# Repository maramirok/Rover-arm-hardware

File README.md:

# Rover Arm Hardware

Custom motor control PCB for the Space Concordia Mars rover robotic arm, designed in KiCad.

## Overview

The board drives five independent DC motors on the rover arm, receives commands over CAN from the main rover controller, and provides regulated power rails for the MCU and peripherals.

## Specifications

- **MCU:** STM32G030C8T6
- **CAN controller/transceiver:** MCP25625 (SPI interface)
- **Motor outputs:** 5 independent channels with PWM speed control and direction signals
- **Power input:** 16V DC
- **Regulation:** Buck converter  + LDO (MCU/logic supply)

## Contents

- `Schematics/` — KiCad schematic files
- `PCB/` — KiCad PCB layout files
- `Gerbers/` — Fabrication output files
- `BOM/` — Bill of materials

## Tools

Designed in KiCad. Open the project file in KiCad to view schematics and layout.

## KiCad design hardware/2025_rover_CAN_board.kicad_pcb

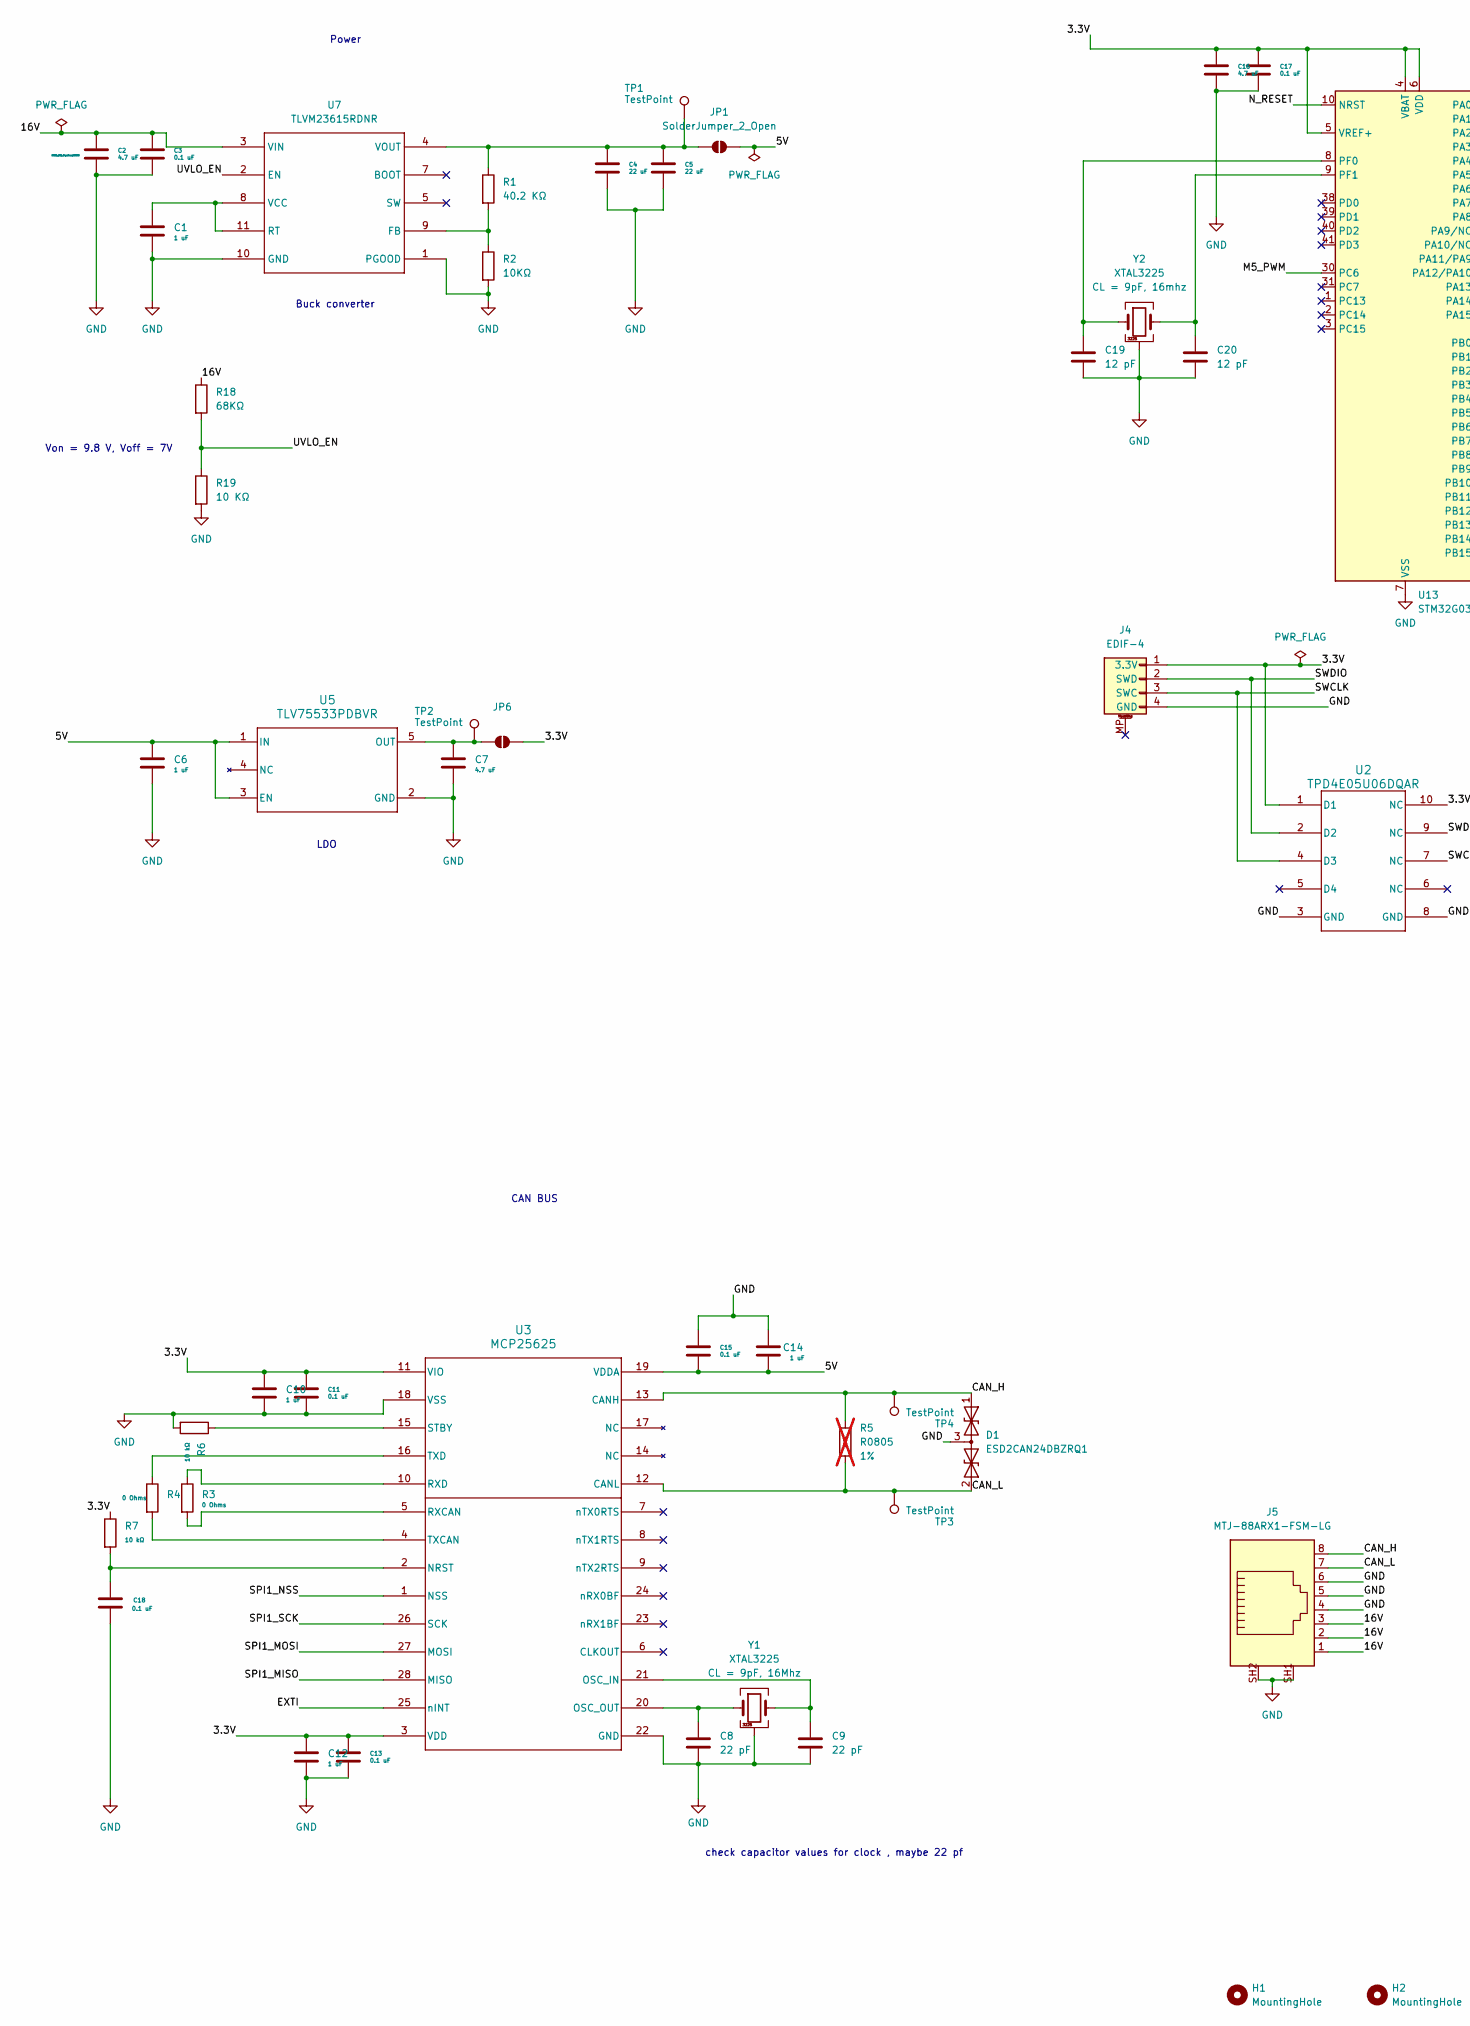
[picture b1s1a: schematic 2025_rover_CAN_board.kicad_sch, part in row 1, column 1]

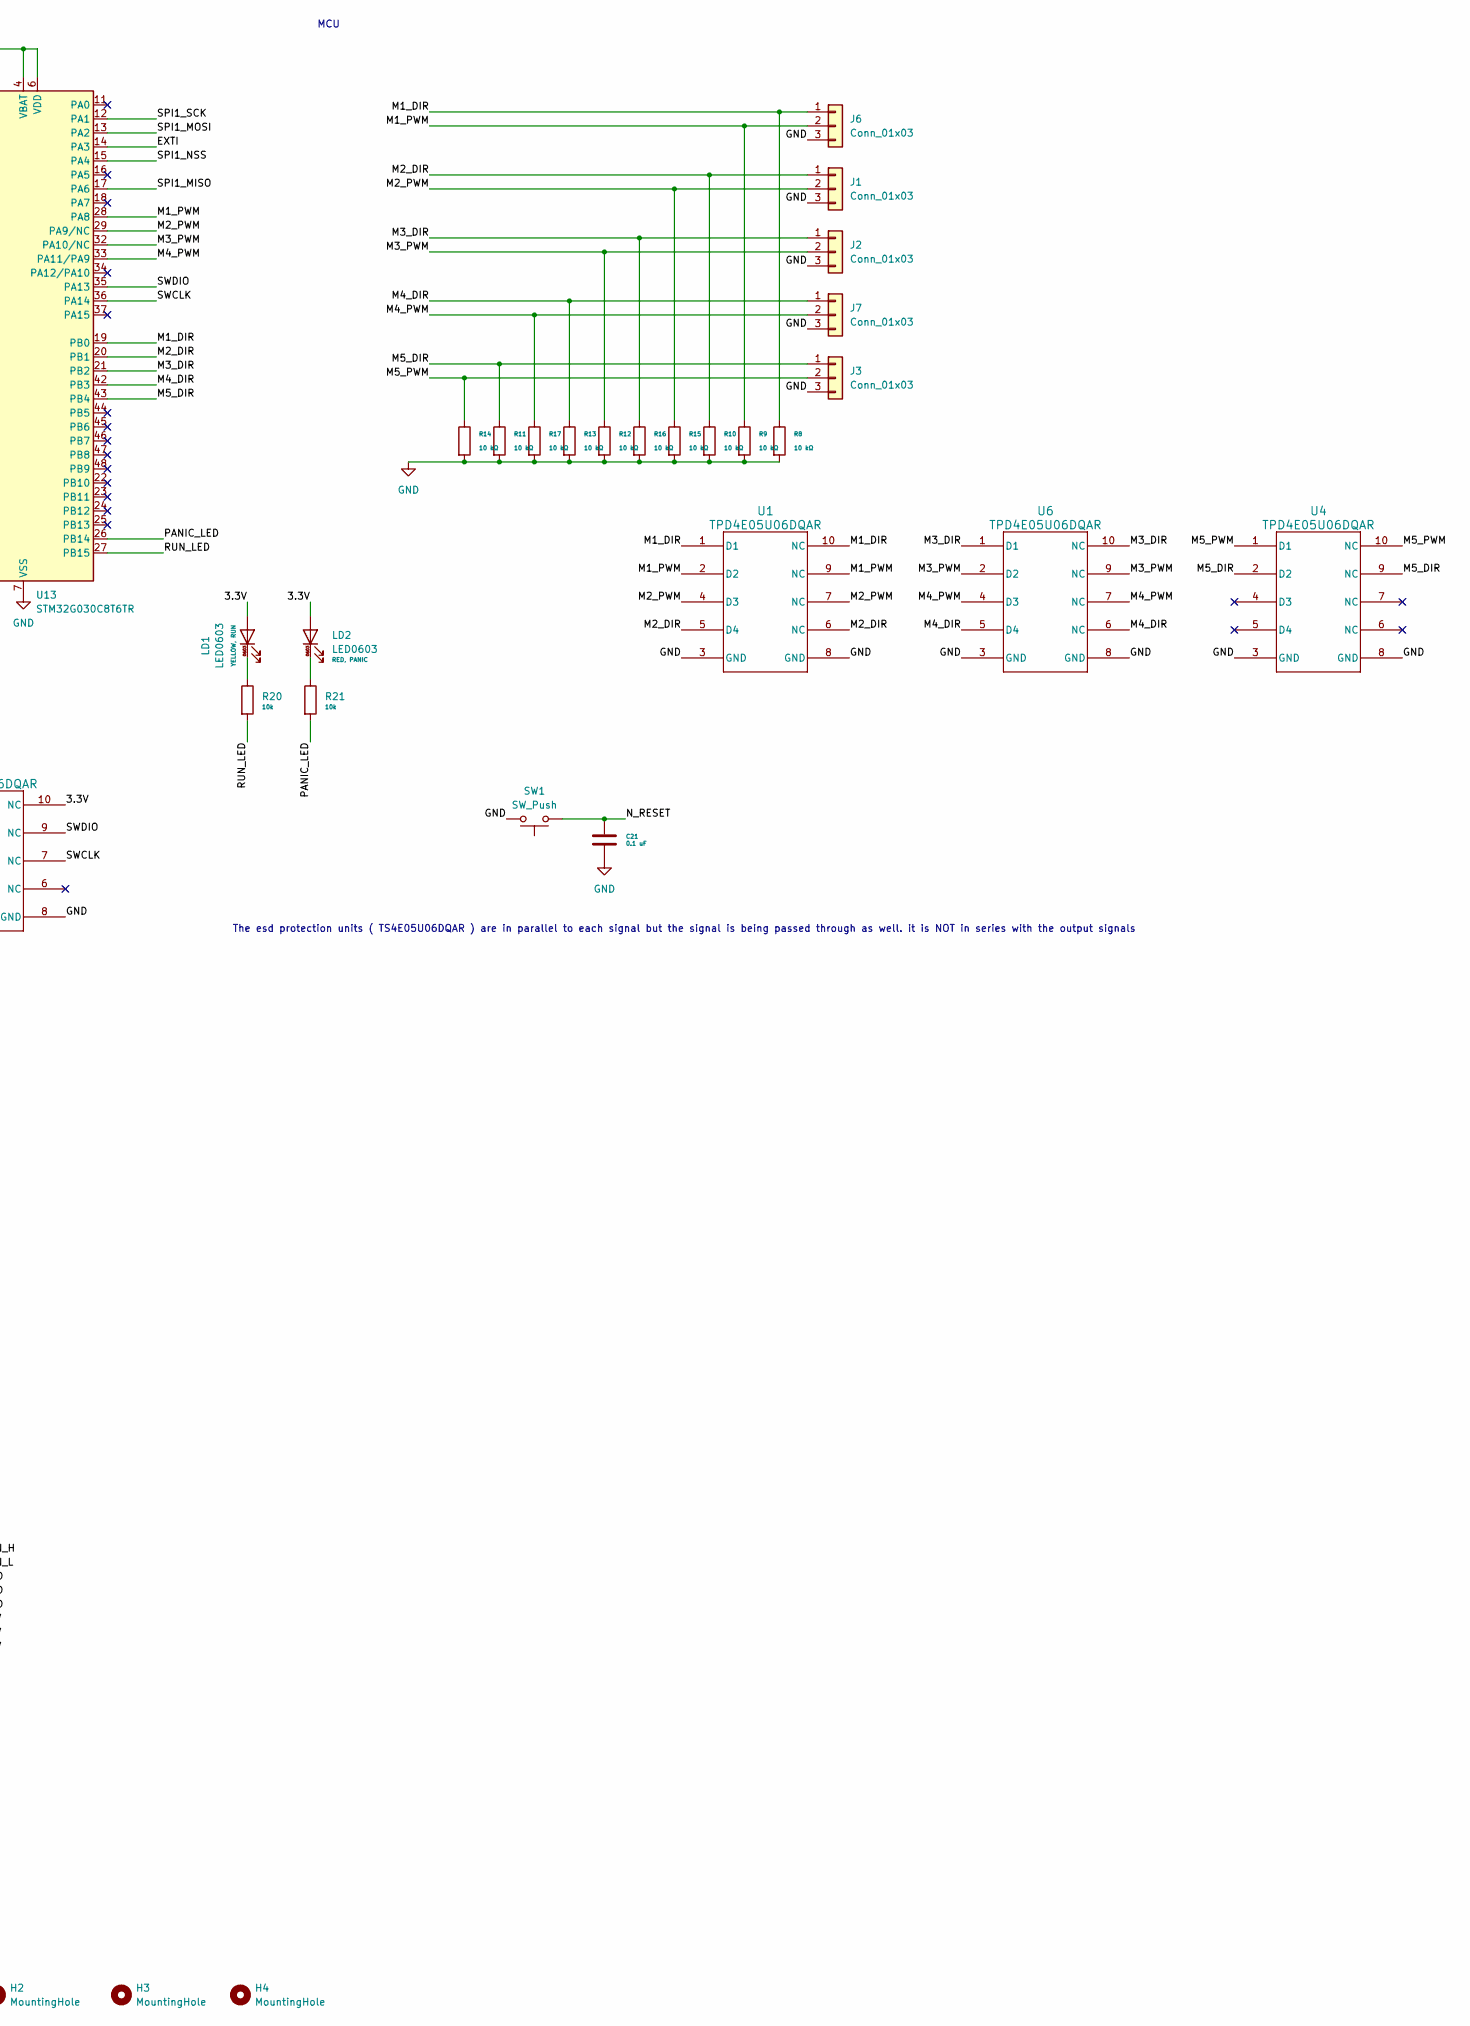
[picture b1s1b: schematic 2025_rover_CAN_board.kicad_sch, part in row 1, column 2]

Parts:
C1, C10, C12, C14: 1 uF; C0402
C2, C7, C16: 4.7 uF; C0805
C3, C11, C13, C15, C17, C18: 0.1 uF; C0402
C4, C5: 22 uF; C0805
C6: 1 uF; C0805
C8, C9: 22 pF; C0402
C19, C20: 12 pF; C0402
C21: 0.1 uF; C0603
D1: ESD2CAN24DBZRQ1; SOT-23_DBZ_TEX
H1, H2, H3, H4: MountingHole; MountingHole_3.2mm_M3
J1, J2, J3, J6, J7: Conn_01x03; JST_XH_S3B-XH-A-1_1x03_P2.50mm_Horizontal
J4: EDIF-4; JST-GH-BM04B-GHS-TBT
J5: MTJ-88ARX1-FSM-LG; ADAMTECH_MTJ-88ARX1-FSM-LG
JP1, JP6: SolderJumper_2_Open; SolderJumper-2_P1.3mm_Open_TrianglePad1.0x1.5mm
LD1, LD2: LED0603
R1: 40.2 KΩ; R0402
R2: 10KΩ; R0402
R3, R4: 0 Ohms; R0402
R5: R0805; not fitted
R6: 10 kΩ; R0805
R7, R8, R9, R10, R11, R12, R13, R14, R15, R16, R17: 10 kΩ; R0402
R18: 68KΩ; R0402
R19: 10 KΩ; R0402
R20, R21: 10k; R0402
SW1: SW_Push; SW_C913791
TP1, TP2, TP3, TP4: TestPoint; TestPoint_Pad_D2.0mm
U1, U2, U4, U6: TPD4E05U06DQAR; DQA0010A
U3: MCP25625; Microchip_ML28
U5: TLV75533PDBVR; DBV0005A
U7: TLVM23615RDNR; RDN0011A
U13: STM32G030C8T6TR; LQFP-48_7x7mm_P0.5mm
Y1, Y2: XTAL3225; SMD3225

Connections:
/3.3V: C10.1, C11.1, C12.1, C13.1, C16.1, C17.1, J4.1 (3.3V), JP6.2 (B), LD1.2 (A), LD2.2 (A), R7.1, U2.1 (D1), U2.10 (NC), U3.3 (VDD), U3.11 (VIO), U13.4 (VBAT), U13.5 (VREF+), U13.6 (VDD)
/5V: C6.1, C14.2, C15.2, JP1.2 (B), U3.19 (VDDA), U5.1 (IN), U5.3 (EN)
/16V: C2.1, C3.1, J5.1, J5.2, J5.3, R18.1, U7.3 (VIN)
/CAN_H: D1.1 (A1), J5.8, R5.1, TP4.1, U3.13 (CANH)
/CAN_L: D1.2 (A2), J5.7, R5.2, TP3.1, U3.12 (CANL)
/EXTI: U3.25 (nINT), U13.14 (PA3)
/M1_DIR: J6.1, R8.1, U1.1 (D1), U1.10 (NC), U13.19 (PB0)
/M1_PWM: J6.2, R9.1, U1.2 (D2), U1.9 (NC), U13.28 (PA8)
/M2_DIR: J1.1, R10.1, U1.5 (D4), U1.6 (NC), U13.20 (PB1)
/M2_PWM: J1.2, R15.1, U1.4 (D3), U1.7 (NC), U13.29 (PA9/NC)
/M3_DIR: J2.1, R16.1, U6.1 (D1), U6.10 (NC), U13.21 (PB2)
/M3_PWM: J2.2, R12.1, U6.2 (D2), U6.9 (NC), U13.32 (PA10/NC)
/M4_DIR: J7.1, R13.1, U6.5 (D4), U6.6 (NC), U13.42 (PB3)
/M4_PWM: J7.2, R17.1, U6.4 (D3), U6.7 (NC), U13.33 (PA11/PA9)
/M5_DIR: J3.1, R11.1, U4.2 (D2), U4.9 (NC), U13.43 (PB4)
/M5_PWM: J3.2, R14.1, U4.1 (D1), U4.10 (NC), U13.30 (PC6)
/N_RESET: C21.1, SW1.1, U13.10 (NRST)
/PANIC_LED: R21.2, U13.26 (PB14)
/RUN_LED: R20.2, U13.27 (PB15)
/SPI1_MISO: U3.28 (MISO), U13.17 (PA6)
/SPI1_MOSI: U3.27 (MOSI), U13.13 (PA2)
/SPI1_NSS: U3.1 (NSS), U13.15 (PA4)
/SPI1_SCK: U3.26 (SCK), U13.12 (PA1)
/SWCLK: J4.3 (SWC), U2.4 (D3), U2.7 (NC), U13.36 (PA14)
/SWDIO: J4.2 (SWD), U2.2 (D2), U2.9 (NC), U13.35 (PA13)
/UVLO_EN: R18.2, R19.1, U7.2 (EN)
GND: C1.2, C2.2, C3.2, C4.2, C5.2, C6.2, C7.2, C8.2, C9.2, C10.2, C11.2, C12.2, C13.2, C14.1, C15.1, C16.2, C17.2, C18.2, C19.2, C20.2, C21.2, D1.3 (common), J1.3, J2.3, J3.3, J4.4 (GND), J5.4, J5.5, J5.6, J5.SH1, J5.SH2, J6.3, J7.3, R2.2, R6.2, R8.2, R9.2, R10.2, R11.2, R12.2, R13.2, R14.2, R15.2, R16.2, R17.2, R19.2, SW1.2, U1.3 (GND), U1.8 (GND), U2.3 (GND), U2.8 (GND), U3.18 (VSS), U3.22 (GND), U3.29 (EPAD), U4.3 (GND), U4.8 (GND), U5.2 (GND), U6.3 (GND), U6.8 (GND), U7.1 (PGOOD), U7.10 (GND), U13.7 (VSS), Y1.2, Y1.4, Y2.2, Y2.4
unnamed: C4.1, C5.1, JP1.1 (A), R1.1, TP1.1, U7.4 (VOUT)
unnamed: C7.1, JP6.1 (A), TP2.1, U5.5 (OUT)
unnamed: LD1.1 (K), R20.1
unnamed: LD2.1 (K), R21.1
unnamed: C18.1, R7.2, U3.2 (NRST)
unnamed: C9.1, U3.21 (OSC_IN), Y1.3
unnamed: C8.1, U3.20 (OSC_OUT), Y1.1
unnamed: R3.2, U3.5 (RXCAN)
unnamed: R3.1, U3.10 (RXD)
unnamed: R6.1, U3.15 (STBY)
unnamed: R4.2, U3.4 (TXCAN)
unnamed: R4.1, U3.16 (TXD)
unnamed: R1.2, R2.1, U7.9 (FB)
unnamed: C1.1, U7.8 (VCC), U7.11 (RT)
unnamed: C19.1, U13.8 (PF0), Y2.1
unnamed: C20.1, U13.9 (PF1), Y2.3

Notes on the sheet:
LDO
check capacitor values for clock , maybe 22 pf
CAN BUS
Buck converter
Von = 9.8 V, Voff = 7V
MCU
Power
The esd protection units ( TS4E05U06DQAR ) are in parallel to each signal but the signal is being passed through as well. it is NOT in series with the output signals

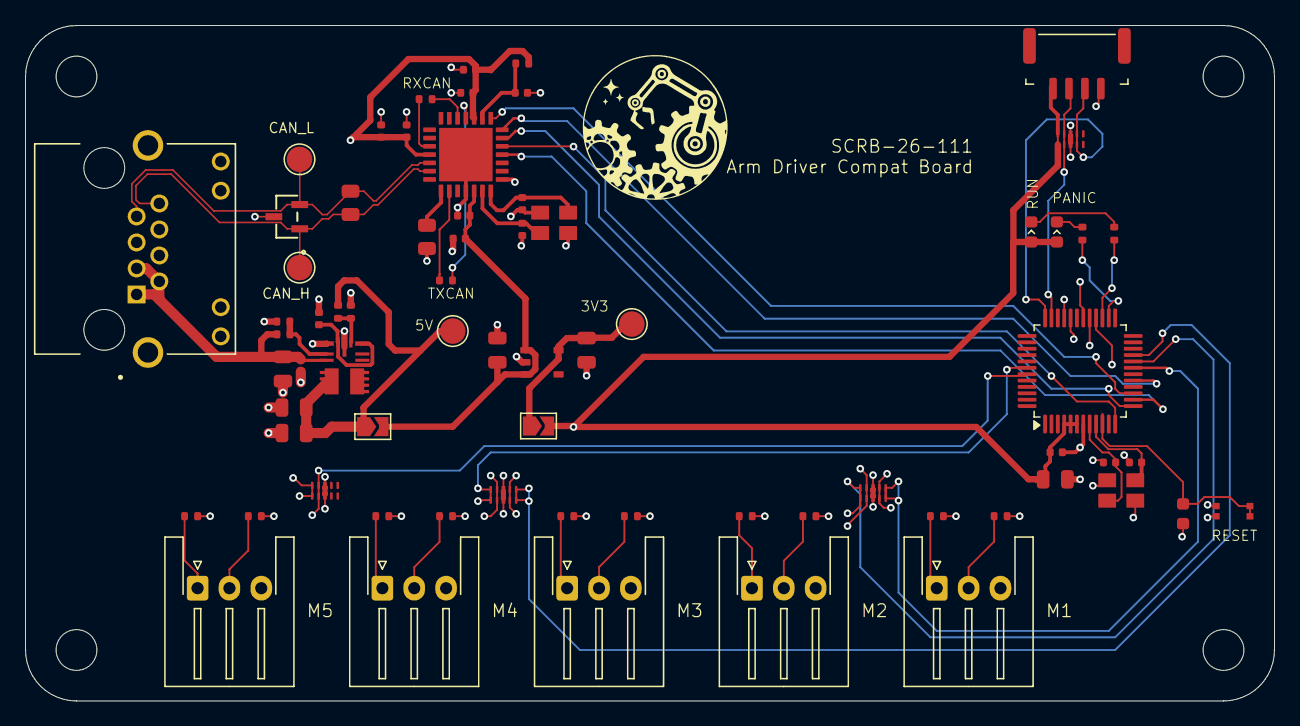
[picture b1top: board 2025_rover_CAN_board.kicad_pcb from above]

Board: 4 copper layers, 98.0 x 53.0 mm, 73 parts (0 on the bottom side), 43 nets.

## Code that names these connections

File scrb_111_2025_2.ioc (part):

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Mcu.Name=STM32G030C(6-8)Tx
Mcu.Package=LQFP48
Mcu.UserName=STM32G030C8Tx
PA0.Signal=GPIO_Analog
PA1.Mode=Full_Duplex_Master
PA1.Signal=SPI1_SCK
PA10.GPIOParameters=GPIO_Label
PA10.GPIO_Label=M3_PWM
PA10.Signal=S_TIM1_CH3
PA11\ [PA9].GPIOParameters=GPIO_Label
PA11\ [PA9].GPIO_Label=M4_PWM
PA11\ [PA9].Signal=S_TIM1_CH4
PA12\ [PA10].Signal=GPIO_Analog
PA13.Mode=Serial_Wire
PA13.Signal=SYS_SWDIO
PA14-BOOT0.Mode=Serial_Wire
PA14-BOOT0.Signal=SYS_SWCLK
PA15.Signal=GPIO_Analog
PA2.Mode=Full_Duplex_Master
PA2.Signal=SPI1_MOSI
PA3.Signal=GPXTI3
PA4.GPIOParameters=PinState,GPIO_Label
PA4.GPIO_Label=CS
PA4.PinState=GPIO_PIN_SET
PA4.Signal=GPIO_Output
PA5.Signal=GPIO_Analog
PA6.Mode=Full_Duplex_Master
PA6.Signal=SPI1_MISO
PA7.Signal=GPIO_Analog
PA8.GPIOParameters=GPIO_Label
PA8.GPIO_Label=M1_PWM
PA8.Signal=S_TIM1_CH1
PA9.GPIOParameters=GPIO_Label
PA9.GPIO_Label=M2_PWM
PA9.Signal=S_TIM1_CH2
PB0.GPIOParameters=GPIO_Label
PB0.GPIO_Label=M1_DIR
PB0.Signal=GPIO_Output
PB1.GPIOParameters=GPIO_Label
PB1.GPIO_Label=M2_DIR
PB1.Signal=GPIO_Output
PB10.Signal=GPIO_Analog
PB11.Signal=GPIO_Analog
PB12.Signal=GPIO_Analog
PB13.Signal=GPIO_Analog
PB14.GPIOParameters=GPIO_Label
PB14.GPIO_Label=PANIC_LED
PB14.Signal=GPIO_Output
PB15.GPIOParameters=GPIO_Label
PB15.GPIO_Label=RUN_LED
PB15.Signal=GPIO_Output
PB2.GPIOParameters=GPIO_Label
PB2.GPIO_Label=M3_DIR
PB2.Signal=GPIO_Output
PB3.GPIOParameters=GPIO_Label
PB3.GPIO_Label=M4_DIR
PB3.Signal=GPIO_Output
PB4.GPIOParameters=GPIO_Label
PB4.GPIO_Label=M5_DIR
PB4.Signal=GPIO_Output
PB5.Signal=GPIO_Analog
PB6.Signal=GPIO_Analog
PB7.Signal=GPIO_Analog
PB8.Signal=GPIO_Analog
PB9.Signal=GPIO_Analog
PC13.Signal=GPIO_Analog
PC14-OSC32_IN\ (PC14).Signal=GPIO_Analog
PC15-OSC32_OUT\ (PC15).Signal=GPIO_Analog
PC6.GPIOParameters=GPIO_Label
PC6.GPIO_Label=M5_PWM
PC6.Signal=S_TIM3_CH1
PC7.Signal=GPIO_Analog
PD0.Signal=GPIO_Analog
PD1.Signal=GPIO_Analog
PD2.Signal=GPIO_Analog
PD3.Signal=GPIO_Analog
PF0-OSC_IN\ (PF0).Mode=HSE-External-Oscillator
PF0-OSC_IN\ (PF0).Signal=RCC_OSC_IN
PF1-OSC_OUT\ (PF1).Mode=HSE-External-Oscillator
PF1-OSC_OUT\ (PF1).Signal=RCC_OSC_OUT
RCC.HSE_VALUE=16000000
RCC.SYSCLKFreq_VALUE=64000000
RCC.SYSCLKSource=RCC_SYSCLKSOURCE_PLLCLK
board=custom

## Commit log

2025-10-30 Create schematic
2025-11-01 Add files via upload
    rough draft of pcb layout, routing still needs to be done
2025-11-02 Create hardware
2025-12-27 Add MCP25625 header file with definitions and types
2026-01-23 Initial commit: STM32 firmware + MCP25625 driver
2026-01-23 Move STM32CubeIDE firmware files into firmware directory
2026-01-23 update to code
2026-01-24 Add .gitignore for firmware build outputs and IDE metadata
2026-01-24 Create .gitignore for build outputs and IDE files
    Add common build outputs and IDE metadata to .gitignore
2026-01-24 Move STM32 project into firmware/ folder
2026-01-31 Add polling-based CAN RX handling and error detection for MCP25625
2026-02-14 Update CAN driver
2026-02-14 Update MCP25625 driver
2026-02-21 Update MCP25625 driver: add frame packing/unpacking
2026-03-12 Updated firmware drivers and header files
2026-03-13 feat: complete motor control firmware with CAN, PWM, and error handling
2026-04-03 your commit message here
2026-04-08 Add error handling state machine with CAN error flags and LED indicators
